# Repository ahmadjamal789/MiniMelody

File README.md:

# 🎹 MiniMelody

**A pocket-sized synth keyboard you can build yourself: 8 keys, a live OLED display, a rotary volume knob, and a real speaker, all on one custom PCB.**

<p align="center">
> Built for **Music Week (Week 3), "Design Your Instrument"**: circuits that turn voltage into sound.
  
</p>

---

## 📖 Table of contents

| Jump to | |
|---|---|
| [What is it?](#-what-is-it) | [Hardware](#-hardware) |
| [Features](#-features) | [Pin map](#-pin-map) |
| [How it works](#-how-it-works) | [Build it yourself](#-build-it-yourself) |
| [Controls](#-controls) | [Design decisions](#-design-decisions) |
| [Project structure](#-project-structure) | [Roadmap](#-roadmap) |

---

## 🎵 What is it?

MiniMelody is a small electronic keyboard. Each of the 8 keys plays its own note, and you can press **several keys at once** to play chords and build up music. A small OLED shows the note and sound you are playing, and the audio comes out of a proper speaker through a digital amplifier, so it sounds much better than a basic buzzer.

Everything (schematic, PCB layout, and firmware) is open, so you can rebuild it, change it, or use it to learn how a synth works.

## ✨ Features

- 🎹 **8 note keys:** one octave, from C up to the high C
- 🎶 **Polyphonic:** the firmware mixes multiple notes at the same time (4 voices planned)
- 🔊 **Real speaker output:** clean digital audio (I2S) into a MAX98357A amplifier
- 📺 **OLED display:** shows the current note, sound type, and volume
- 🎛️ **Rotary encoder** for volume, plus **MODE** and **OCT** buttons for sound and octave
- 🧩 **Custom KiCad PCB:** keys, display, speaker, and controller on a single board
- 🔌 **Powered over USB** through the Pico's own port, no battery needed

## ⚙️ How it works

```mermaid
flowchart LR
    K["8 note keys"] --> P
    C["MODE / OCT buttons<br/>Rotary encoder"] --> P
    P["Raspberry Pi Pico<br/>(RP2040)"] -- "I2C" --> D["OLED display"]
    P -- "I2S digital audio" --> A["MAX98357A<br/>amplifier"]
    A --> S["Speaker"]
    U["USB 5 V"] --> P
    P -- "VBUS 5 V" --> A
```

1. **Scan:** the Pico checks every button many times per second. Each button connects its pin to ground when pressed (the Pico's internal pull-up resistors do the rest).
2. **Generate:** for every key held down, the firmware reads a stored waveform (sine, square, saw, or triangle) at that note's frequency and shapes it with a simple volume envelope so notes don't click.
3. **Mix:** the active notes are added together and scaled to avoid distortion.
4. **Play:** the mixed audio is sent to the amplifier over I2S, and the amplifier drives the speaker.
5. **Show:** the OLED updates a few times per second with what is playing.

## 🎛️ Controls

| Control | What it does |
|---|---|
| **8 note keys** | Play C, D, E, F, G, A, B, and high C (hold several for chords) |
| **MODE button** | Cycles through sounds (square, saw, triangle, sine, and so on) |
| **OCT button** | Shifts the whole keyboard up or down an octave |
| **Rotary encoder** | Turn to change the volume |

## 🧰 Hardware

<details>
<summary><b>Bill of materials</b> (click to expand)</summary>

| Qty | Part | Notes |
|---|---|---|
| 1 | Raspberry Pi Pico (RP2040) | Main controller, also provides USB power |
| 1 | MAX98357A I2S amplifier breakout | Drives the speaker |
| 1 | Small speaker, 4 or 8 ohm, about 28 mm | Wired to the 2-pin speaker header |
| 1 | 0.96" 128x64 OLED (SSD1306, I2C) | 4-pin module |
| 10 | Tactile push buttons | 8 note keys, plus MODE and OCT |
| 1 | Rotary encoder | Volume |
| 1 | 10 uF capacitor | Amplifier supply decoupling |
| 1 | 100 nF capacitor | Supply decoupling |
| 1 | 2-pin header | Speaker connection |
| 1 | Custom PCB | Files in `hardware/` |

</details>

### 🔌 Pin map

<details>
<summary><b>Raspberry Pi Pico connections</b> (click to expand)</summary>

| Function | Pico pins | Notes |
|---|---|---|
| I2S DIN / BCLK / LRCLK | GP13 / GP14 / GP15 | LRCLK must be the pin right after BCLK |
| OLED SDA / SCL | GP0 / GP1 | I2C0 |
| Note keys, MODE, OCT, encoder | See `hardware/` schematic | Each button connects its pin to GND |
| Amplifier power | VBUS (5 V) | |
| OLED power | 3V3_OUT | |

> Always check this table against the final schematic in `hardware/`, which is the source of truth.

</details>

## 🗂️ Project structure

```
MiniMelody/
├── hardware/        # KiCad project: schematic, PCB, footprints, 3D models
│   └── gerbers/     # Manufacturing files for ordering the PCB
├── firmware/        # PlatformIO project for the Pico
├── docs/
│   └── images/      # Photos and 3D renders
└── README.md
```

## 🔨 Build it yourself

### 1. Hardware

1. Open the project in **KiCad** and run the Electrical Rules Check and the Design Rules Check. Both should come back clean.
2. Export the **Gerber and drill files** (File > Plot) and send them to a PCB manufacturer.
3. Solder the parts. A good order is: capacitors, buttons, headers, amplifier, Pico, display, and finally the speaker wires.
4. Connect the speaker to the 2-pin header (the amplifier output has no polarity requirement for a basic speaker).

### 2. Firmware

You need [PlatformIO](https://platformio.org/) (VS Code extension or CLI).

```bash
cd firmware
pio run                 # build
pio run -t upload       # flash
```

To flash, hold the **BOOTSEL** button on the Pico while plugging in the USB cable, then run the upload command.

### 3. Play

Plug in USB, wait for the display to light up, and press the keys. 🎶

## 🧠 Design decisions

- **Why a Pico and not an Arduino?** A basic Arduino `tone()` can only play one note at a time. The RP2040 is fast enough to mix several notes in software and stream audio over I2S.
- **Why I2S and an amplifier chip?** Digital audio is much cleaner and louder than PWM into a buzzer.
- **Why no diodes or button matrix?** The Pico has enough pins to give every button its own, so every chord works and the schematic stays simple.
- **Why no pull-up resistors?** The Pico has internal pull-ups on every pin, and the firmware turns them on.
- **Why power the amplifier from 5 V?** It gives the speaker more headroom and volume than 3.3 V.

## 🗺️ Roadmap

- [x] Concept and parts selection
- [x] Schematic in KiCad
- [x] PCB layout and routing
- [ ] Final design checks and PCB order
- [ ] Firmware: button scanning and single-note tone
- [ ] Firmware: polyphonic mixing
- [ ] Firmware: OLED display and sound modes
- [ ] 3D-printed or laser-cut enclosure
- [ ] Demo video

## 🤝 Contributing

Ideas and improvements are welcome. Open an issue or a pull request.

## 👤 Author

Made by **Ahmad Adesoye** · [GitHub](https://github.com/ahmadjamal789)

---

<p align="center"><i>Make. Some. Noooooooooise.</i></p>

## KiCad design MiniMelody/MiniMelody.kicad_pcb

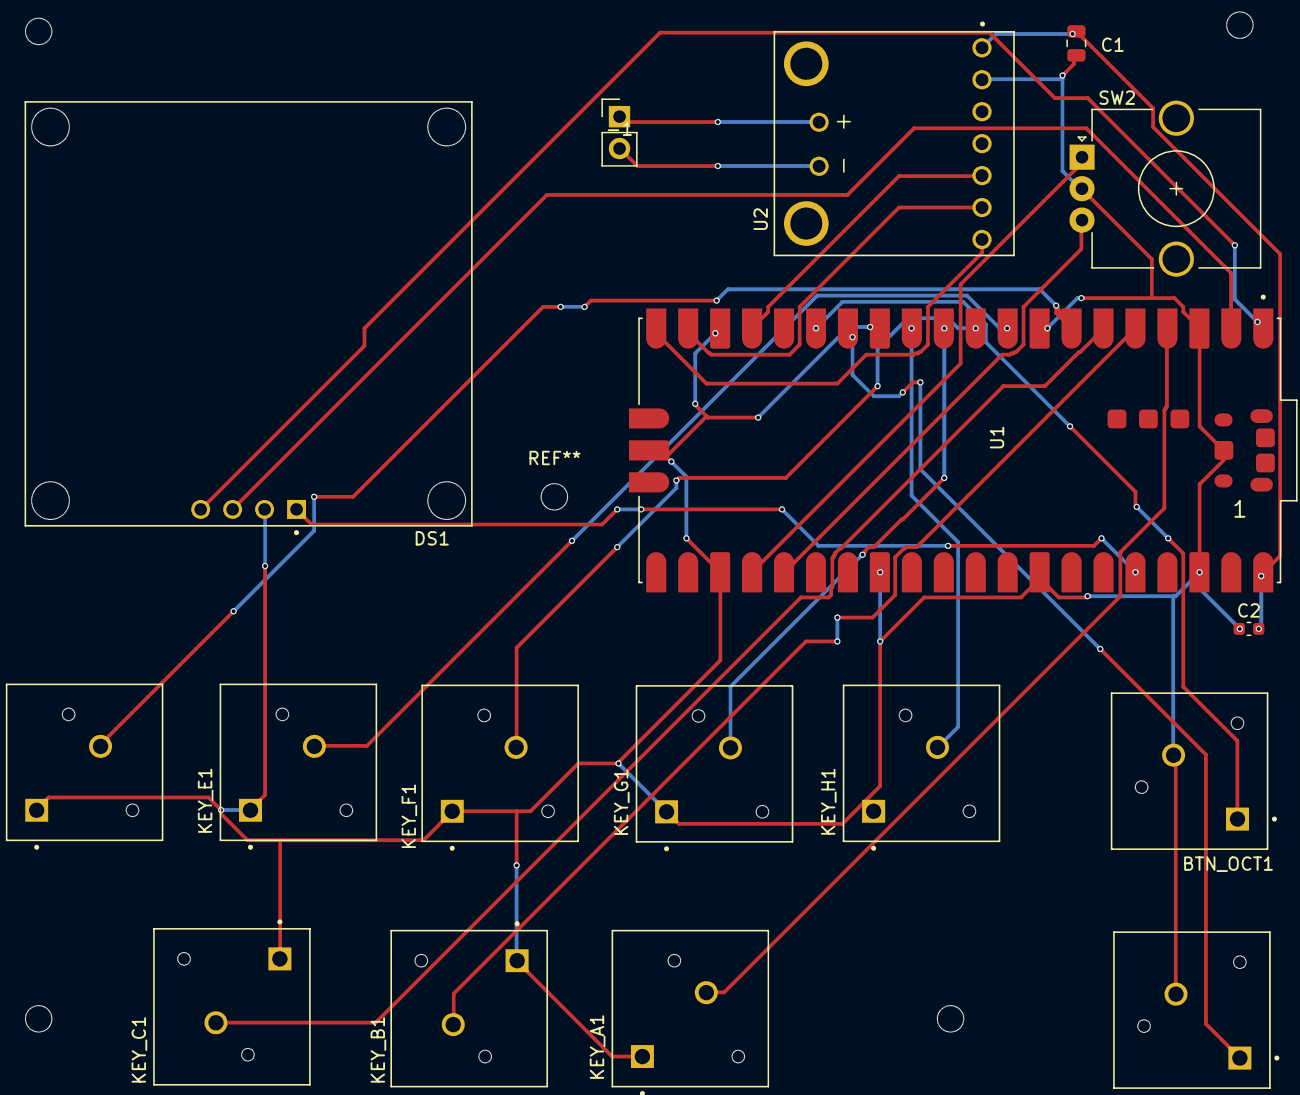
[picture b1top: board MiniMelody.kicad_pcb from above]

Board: 2 copper layers, 17 parts (0 on the bottom side), 22 nets.

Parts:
-1: Speaker pin; PinHeader_1x02_P2.54mm_Vertical
BTN_MODE1: 320.01E11WHT; SW_320.01E11WHT
BTN_OCT1: 320.01E11WHT; SW_320.01E11WHT
C1: 10uF; C_0805_2012Metric
C2: 100nF; C_0603_1608Metric
DS1: OLED_Display; LCD_OLED_128X64_1.3_I2C
KEY_A1: 320.01E11WHT; SW_320.01E11WHT
KEY_B1: 320.01E11WHT; SW_320.01E11WHT
KEY_C1: 320.01E11WHT; SW_320.01E11WHT
KEY_D1: 320.01E11WHT; SW_320.01E11WHT
KEY_E1: 320.01E11WHT; SW_320.01E11WHT
KEY_F1: 320.01E11WHT; SW_320.01E11WHT
KEY_G1: 320.01E11WHT; SW_320.01E11WHT
KEY_H1: 320.01E11WHT; SW_320.01E11WHT
SW2: RotaryEncoder; RotaryEncoder_Alps_EC12E_Vertical_H20mm_CircularMountingHol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
U1: pi-Pico; MODULE_SC0917
U2: Sound Amp; MODULE_3006

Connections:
+3.3V: DS1.1 (VDD), U1.36 (3V3_OUT)
+5V: C1.1, C2.2, U1.40 (VBUS), U2.JP1_1 (VDD)
GND: BTN_MODE1.3, BTN_OCT1.3, C1.2, C2.1, DS1.2 (GND), KEY_A1.1, KEY_B1.1, KEY_C1.1, KEY_D1.1, KEY_E1.1, KEY_F1.1, KEY_G1.1, KEY_H1.1, SW2.C, U1.3 (GND), U1.8 (GND), U1.13 (GND), U1.18 (GND), U1.23 (GND), U1.28 (GND), U1.33 (AGND), U1.38 (GND), U1.D2 (GND), U1.TP1 (TP1_GND), U2.JP1_2 (GND)
unnamed: -1.1, U2.X1_2 (VO+)
unnamed: -1.2, U2.X1_1 (VO-)
unnamed: DS1.3 (SCK), U1.2 (GP1)
unnamed: DS1.4 (SDA), U1.1 (GP0)
unnamed: KEY_A1.3, U1.4 (GP2)
unnamed: KEY_B1.3, U1.5 (GP3)
unnamed: KEY_C1.3, U1.6 (GP4)
unnamed: KEY_D1.3, U1.7 (GP5)
unnamed: KEY_E1.3, U1.9 (GP6)
unnamed: KEY_F1.3, U1.10 (GP7)
unnamed: KEY_G1.3, U1.11 (GP8)
unnamed: KEY_H1.3, U1.12 (GP9)
unnamed: BTN_MODE1.1, U1.14 (GP10)
unnamed: BTN_OCT1.1, U1.15 (GP11)
unnamed: U1.17 (GP13), U2.JP1_5 (DIN)
unnamed: U1.19 (GP14), U2.JP1_6 (BCLK)
unnamed: U1.20 (GP15), U2.JP1_7 (LRCLK)
unnamed: SW2.A, U1.24 (GP18)
unnamed: SW2.B, U1.25 (GP19)

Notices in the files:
README.md:
License: MIT
